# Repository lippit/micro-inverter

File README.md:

# An open-source - community built micro-inverter

## Manifesto 

The project goal are : 

- Having the first open source PV micro-inverter
- Finally a design easy to repair that is no longer a black box
- Redeem your data sovereignty, you will no longer depend on a proprietary cloud to follow your solar production and consumption. 

## Open, for everyone, forever

- This project is propulsed by its community. 
- The collective work generated is meant to remain open. 
- Design files are made with open source software - Namely kiCAD.
- Mechanical interfaces and components are modeled using FreeCAD.
- Simulation files use ngSpice.

In that sense, the owntech foundation aims at protecting this technical common.

## Specifications
This section is inspired from 

Comparison of micro-inverters with rated output power between 350VA and 400VA:

| Model                                  | HM-350 | HM-400 | IQ7A |EVT300  |TSOL-M800  |
|:---------------------------------------|:-----------:|:-----------:|:-----------:|:-------------:|:---------------:|
| Manufacturer                           | Hoymiles    | Hoymiles    | Enphase     | Envertech     |    TSUN         |
| Number of solar panels                 | 1           | 1           | 1           | 1             | 2               |
| Recommended input power (W)            | 280-470+    | 320-540+    | 295-460     | 180-420+      |2 $\cdot$ 280-440|
| $V_{MPPT,min}$ (V)                     | 33          | 34          | 38 (18)     | 24            | 33              |
| $V_{MPPT,max}$ (V)                     | 48          | 48          | 43 (58)     | 45            | 48              |
| Start-up voltage (V)                   | 22          | 22          | 22          | -             | -               |
| Operating volage range (V)             | 16-60       | 16-60       | 16-58       | 18-54         | 16-60           |
| Maximum input current (A)              | 11.5        | 12          | 12          | 12            | 11.5            |
| Maximum input short circuit current (A)| 15          | 15          | 20          | 15            | 15              |
| Rated output power (VA)                | 350         | 400         | 349         | 300           | 600             |
| Peak efficiency (%)                    | 96.7        | 96.7        | 97.7        | 95.4          | 96.7            |
| CEC weighted efficiency (%)            | 96.5        | 96.5        | 97.0        | 95.0          | 96.5            |

### uVerter Target specifications

| Category | Requirement | Notes |
|---|---:|---|
| Grid | 220 V AC to 250V AC / 50 to 60 Hz   | Hardware not compatible with 110V grids |
| Grid compliance | Grid-code compliant | Exact certification scope depends on country / standard |
| Rated apparent power | 450 VA | Software-limited power cap supported |
| Input DC operating range | 16 V – 58 V | PV module operating window |
| Recommended PV input power | 350 W – 550 W | Depends on module and thermal conditions |
| Efficiency | > 95% | Target at nominal conditions |
| Power factor | ≈ 1 | Near-unity PF at rated power |
| THD | < 5% | Total harmonic distortion at rated conditions |
| Isolation | Galvanic isolation | Electrical isolation between PV and grid |
| Operating temperature | -40 °C to +60 °C | Derating may apply |
| Repairability | No invasive potting | Designed to be serviceable / inspectable |
| Connectivity | Wi-Fi | Local-first monitoring (no proprietary cloud required) |

## Renderings

## Control overview

The control overview shows the uVerter as two coordinated stages: a PV-controlled DC/DC front end that regulates the panel operating point and raises the DC bus, followed by an AC control stage that shapes a grid-compliant AC output. Measurements and commands flow through Data I/O and the grid-compliance controller so the inverter can synchronize to line/neutral, limit harmonics, and maintain safe operation while power flows from the PV input to the grid.

## Firmware overview

The `firmware/src/main.cpp` file is the entry point for the uVerter firmware: it configures the sensors and power stages, sets up the real-time and background tasks, and runs the state machine plus control loops that drive the boost and inverter legs based on measurements and synchronization status.

- Real-time control runs in `loop_critical_task()` at 100 µs to read sensors, enforce protections, regulate the boost stage, compute duty cycles, and update grid-sync variables.
- Supervisory logic runs in `loop_application_task()` to manage modes (idle/startup/power/error), handle transitions, and expose telemetry through the user data API.

### Compiling

Micro-inverter uses [PlatformIO](https://platformio.org/) as it's build and dependency management system.

#### From the command line

1. Create and activate a Python virtual environment.

        python3 -m venv .owntech-venv
        source .owntech-venv/bin/activate

2. Install PlatformIO.

        pip3 install platformio

3. Compile the code. Dependencies (including Zephyr and Owntech libraries) are downloaded automatically.

        cd micro-inverter/firmware/
        pio run

#### In Visual Studio Code

1. Install the "PlatformIO IDE" extension
2. Open the `firmware` directory via PlatformIO's home screen (**not** with VSCode's File -> Open)
3. Press the "Build" button in the PlatformIO toolbar (found on the bottom left)

## Contribute 

### Spread the word

- ⭐ Star this repository  

- Share the project with PV / power electronics / open-hardware communities  

- Mention it in meetups, forums, maker spaces, or your local energy co-op  

### Give feedback and report issues

Help us improve by opening GitHub issues:

- Bug reports (schematic/PCB mistakes, BOM mismatches, mechanical interferences)  

- Documentation gaps (unclear steps, missing diagrams, confusing naming)  

- Feature requests  

### Choose a contribution path

Start with  — a living list of work items the community can pick up.  
Whether you’re a student looking for a thesis topic, an engineer wanting to review a safety-critical design, or a maker growing skills in hardware and firmware: you’re welcome here.  

Bring what you have: time, curiosity, test equipment, careful eyes, lived experience installing or repairing PV gear.  
Let’s build an inverter that isn’t a black box — and keep it open, for everyone, forever.  

## Safety first  

### Disclaimer
This project is shared as-is, without any warranty of any kind, and without any guarantee of compliance with safety, EMC, or grid-connection regulations.
By building, modifying, or using this design, you accept full responsibility for verification, testing, certification (if applicable), and safe operation.

Do not connect a prototype to the public grid.
Grid connection must only happen after appropriate validation, protections, and (where required) third-party certification.

### Mind the risks  
Building a micro-inverter is an advanced DIY project. It combines high energy, high voltage, fast switching, and grid interaction — a mix that can injure, start fires, or damage property

Key hazards include:

- Electric shock and electrocution
Internal stages can reach hundreds of volts. Multiple nets are high voltage. Some capacitors can stay charged after power-off. Treat the system as live until proven discharged and measured.

- Fire and thermal runaway
Faults can turn traces, connectors, inductors, or semiconductors into heaters in seconds. Thermal issues can escalate quickly.

### A community note
We want this project to be open — not reckless. If you spot a safety issue (creepage/clearance, insulation, thermal margins, protection logic, connector ratings, etc.), please report it.
Safety improvements are contributions that protect everyone.

## Standards and directives

### Relevant EU directives for CE

- Directive 2001/95/EC: General Product Safety
- Directive 2014/30/EU: Electromagnetic Compatibility (EMC)
- Directive 2014/35/EU: Low Voltage (LVD)
- Directive 2014/53/EU: Radio Equipment (RED)
- Directive 2011/65/EU: Restriction of the use of certain Hazardous Substances (RoHS)

### Low Voltage Directive (LVD)

**EN IEC 62109-1:2010**
Safety of power converters for use in photovoltaic power systems - Part 1: General requirements

**EN IEC 62109-2:2011**
Safety of power converters for use in photovoltaic power systems - Part 2: Particular requirements for inverters

### Electromagnetic Compatibility (EMC)

**EN 62920:2017+A11+A1:2021**
Photovoltaic power generating systems - EMC requirements and test methods for power conversion equipment

**ETSI EN 301 489-1**
ElectroMagnetic Compatibility (EMC) standard for radio equipment and services; Part 1: Common technical requirements

**ETSI EN 301 489-17**
ElectroMagnetic Compatibility (EMC) standard for radio equipment and services; Part 17: Specific conditions for Broadband Data Transmission Systems

### Radio Equipment Directive (RED)

**ETSI EN 300 328 V2.2.2**
Wideband transmission systems; Data transmission equipment operating in the 2,4 GHz band; Harmonised Standard for access to radio spectrum

### Grid Regulations

As grid regulations are country specific, please refer to 

## Licence 

This project is licenced under **CERN-OHL-V2-S** open source hardware licence. Licence file can be found under `License/cern-ohl-v2-s`.

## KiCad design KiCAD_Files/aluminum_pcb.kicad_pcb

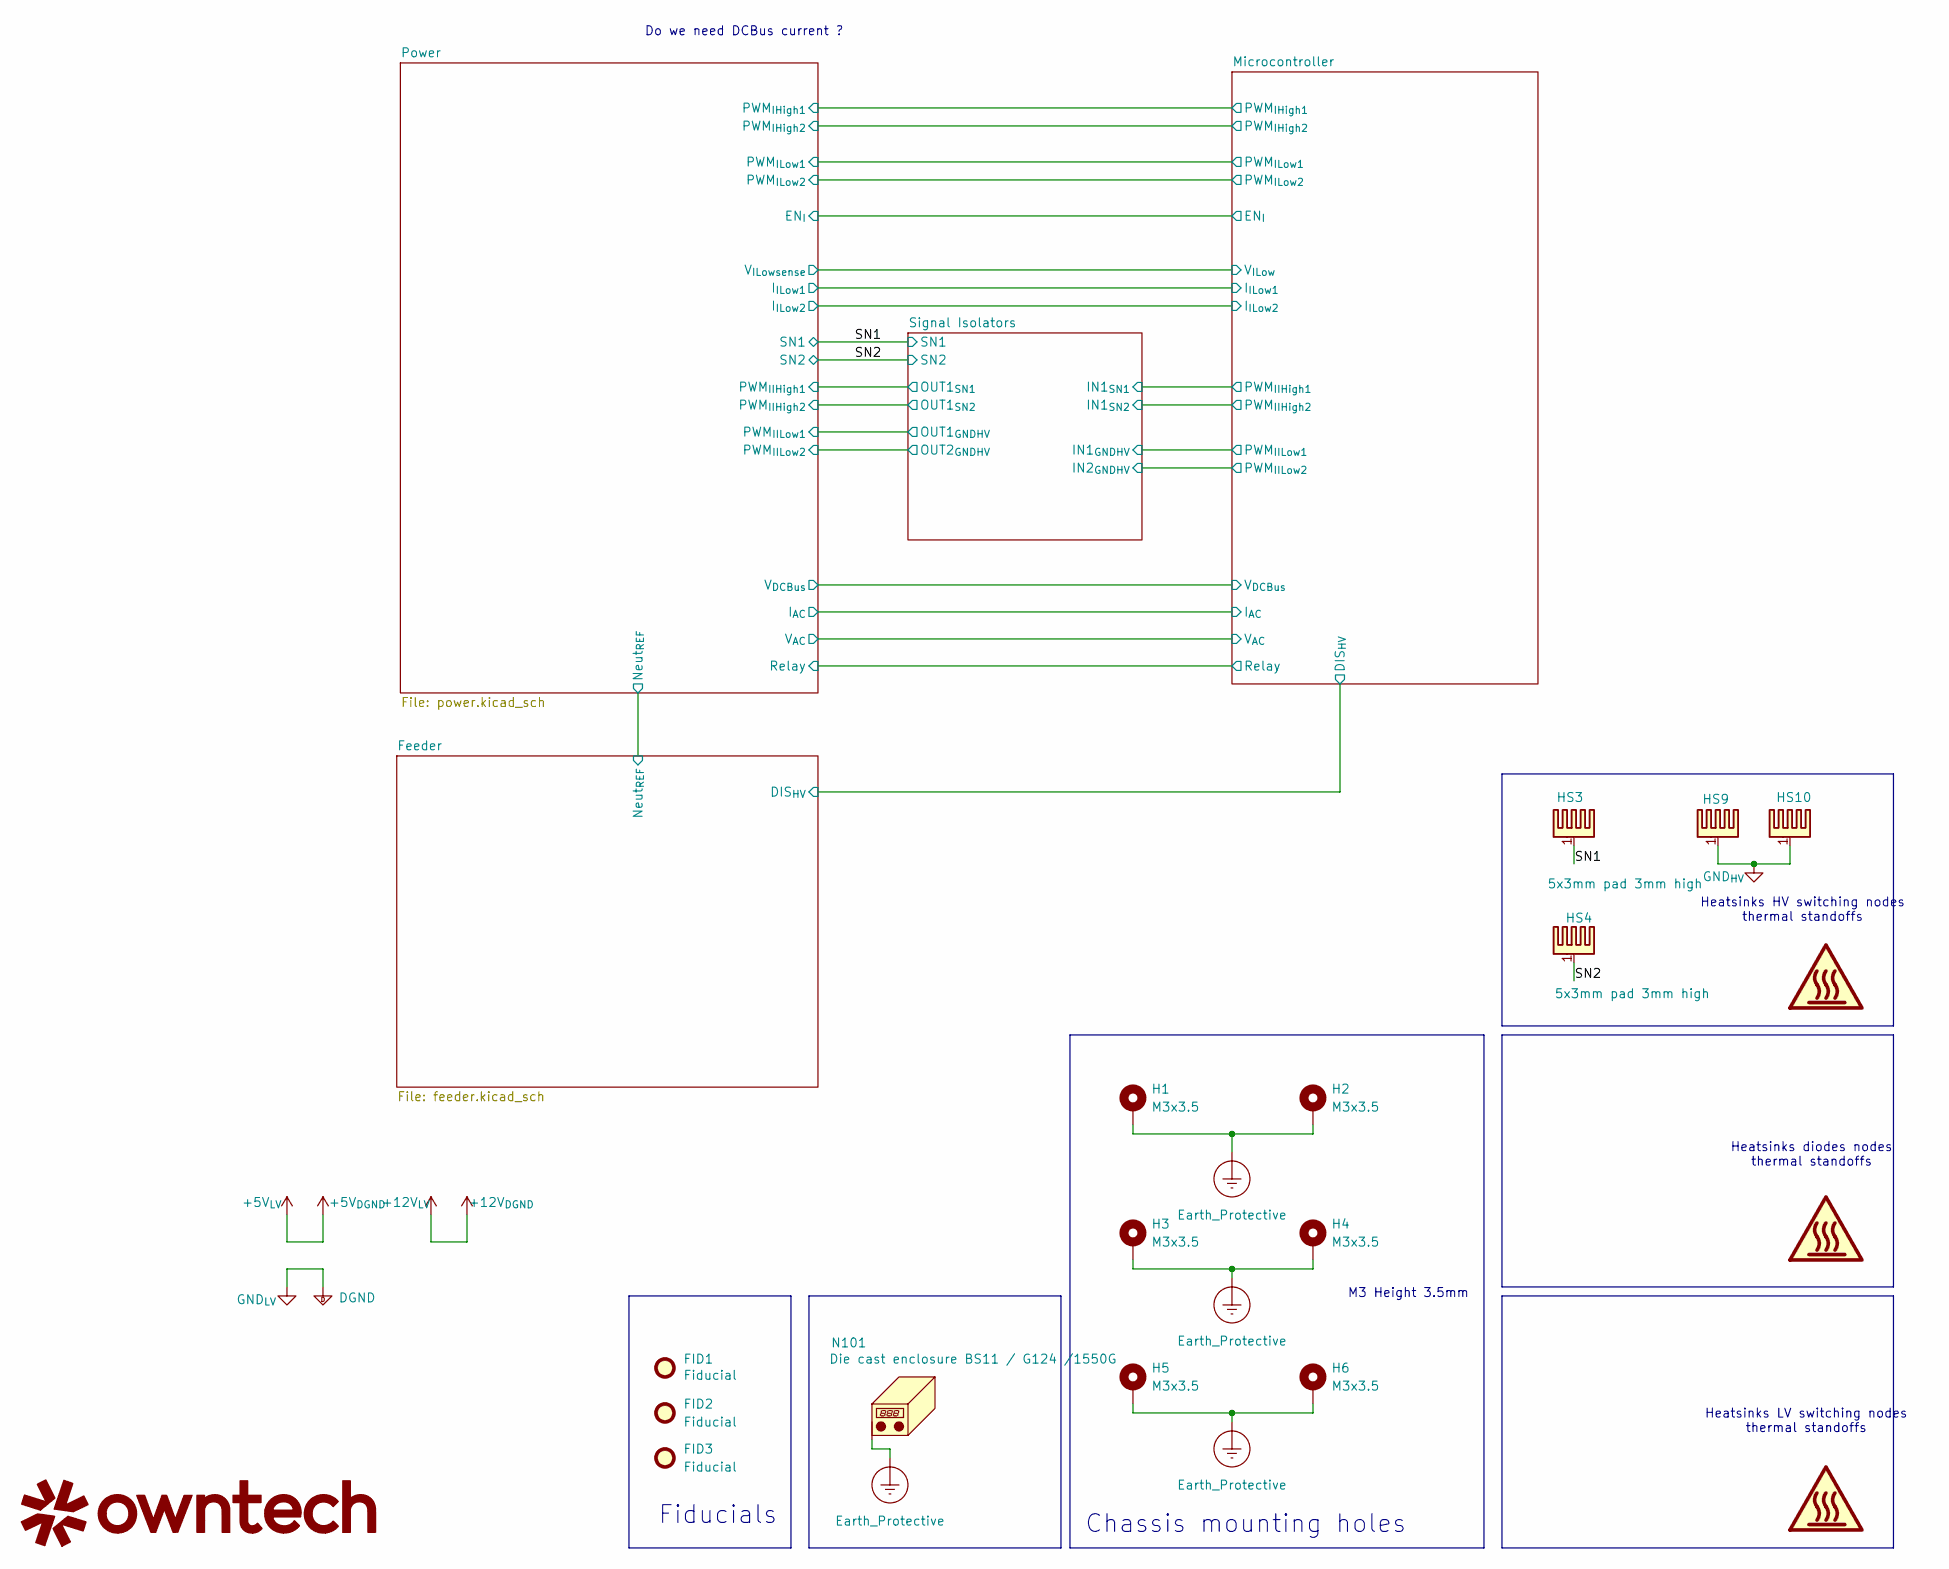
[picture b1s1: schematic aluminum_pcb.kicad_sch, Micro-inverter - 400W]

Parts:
FID1, FID2, FID3: Fiducial; Fiducial_1mm_Mask2mm
H1, H2, H3, H4, H5, H6: M3x3.5; SMD_BD5.6-D4.1; LCSC C2916333
HS3, HS4, HS9, HS10: 5x3mm pad 3mm high; BTC-533-ZN01; LCSC C42404563
Logo1: owntech34mmneg
N101: Die cast enclosure BS11 / G124 /1550G; Die Cast Casing 1550G

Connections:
/SN1: HS3.1; also elsewhere on the board
/SN2: HS4.1; also elsewhere on the board
Earth_Protective: H1.1, H2.1, H3.1, H4.1, H5.1, H6.1, N101.1; also elsewhere on the board
GND_{HV}: HS9.1, HS10.1; also elsewhere on the board

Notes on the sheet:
Heatsinks diodes nodes thermal standoffs
Heatsinks HV switching nodes thermal standoffs
M3 Height 3.5mm
Do we need DCBus current ?
Fiducials
Chassis mounting holes
Heatsinks LV switching nodes thermal standoffs

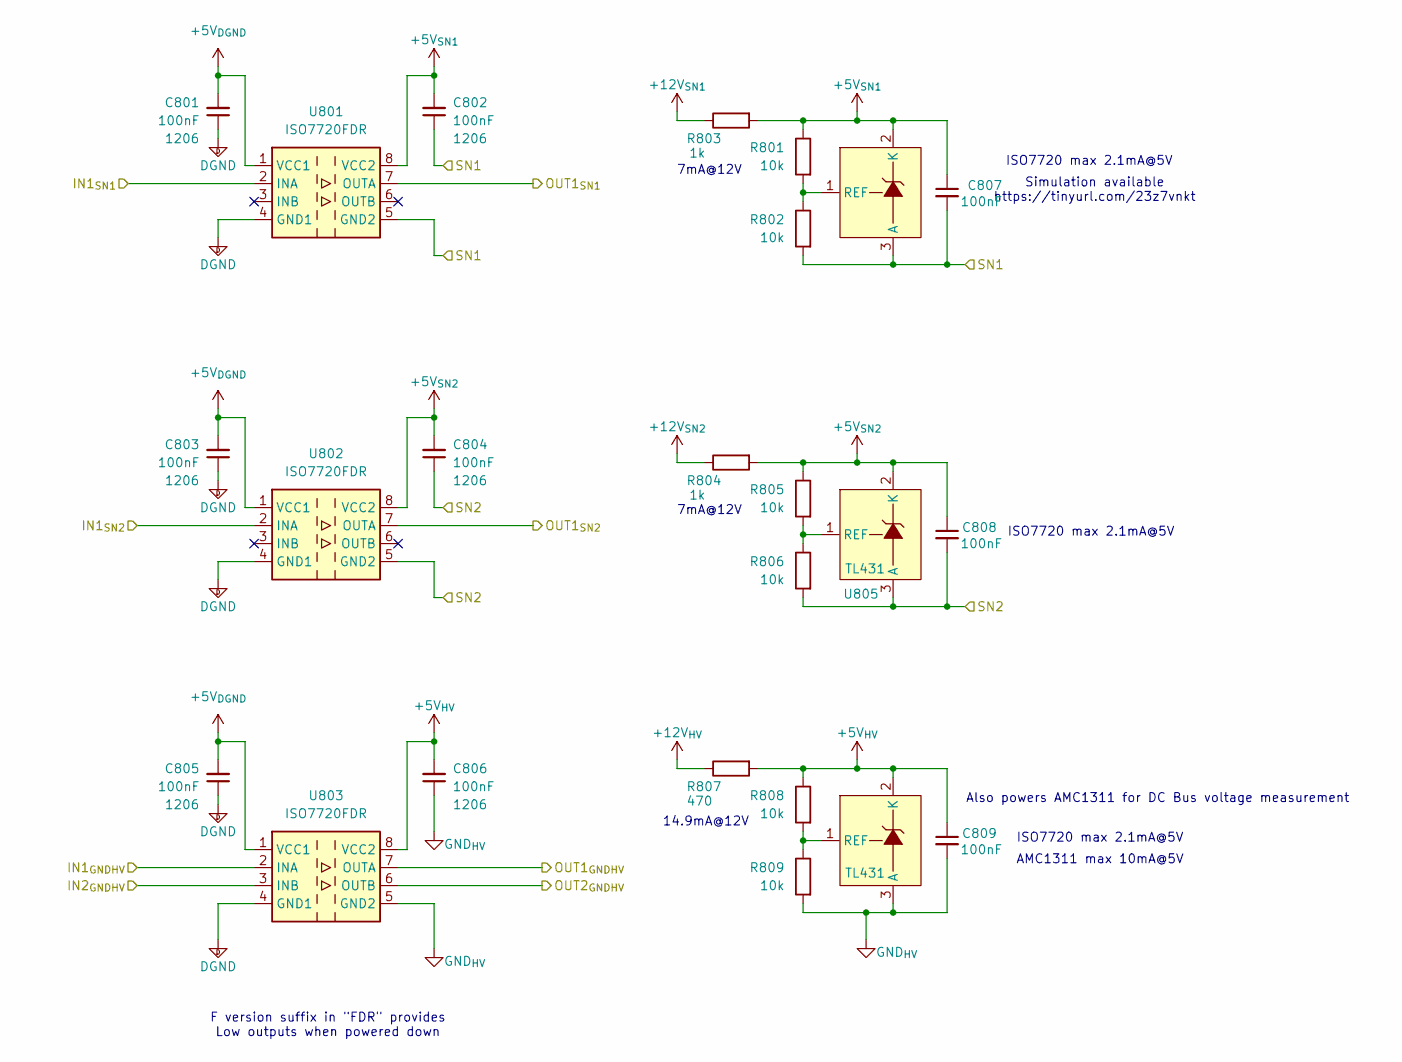
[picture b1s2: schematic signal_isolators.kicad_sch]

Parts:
C801, C802, C803, C805, C806: 100nF; C_1206_3216Metric; Voltage 50V; LCSC C5449000
C804, C807, C808, C809: 100nF; C_0805_2012Metric; Voltage 50V; LCSC C5449000
R801, R802, R805, R806, R808, R809: 10k; C_0805_2012Metric
R803, R804: 1k; C_0805_2012Metric
R807: 470; C_0805_2012Metric
U801, U802, U803: ISO7720FDR; SOIC-8_3.9x4.9mm_P1.27mm; LCSC C2878308
U804: TL431DBZ; SOT-23
U805, U806: TL431; SOT-23

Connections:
+5V_{DGND}: C801.2, C803.2, C805.2, U801.1 (VCC1), U802.1 (VCC1), U803.1 (VCC1); also elsewhere on the board
+5V_{HV}: C806.2, C809.1, R807.2, R808.1, U803.8 (VCC2), U806.2 (K); also elsewhere on the board
+5V_{SN1}: C802.2, C807.1, R801.1, R803.2, U801.8 (VCC2), U804.2 (K)
+5V_{SN2}: C804.2, C808.1, R804.2, R805.1, U802.8 (VCC2), U805.2 (K)
+12V_{HV}: R807.1; also elsewhere on the board
+12V_{SN1}: R803.1; also elsewhere on the board
+12V_{SN2}: R804.1; also elsewhere on the board
/Microcontroller/PWM_{IIHigh1}: U801.2 (INA); also elsewhere on the board
/Microcontroller/PWM_{IIHigh2}: U802.2 (INA); also elsewhere on the board
/Microcontroller/PWM_{IILow1}: U803.2 (INA); also elsewhere on the board
/Microcontroller/PWM_{IILow2}: U803.3 (INB); also elsewhere on the board
/Power/PWM_{IIHigh1}: U801.7 (OUTA); also elsewhere on the board
/Power/PWM_{IIHigh2}: U802.7 (OUTA); also elsewhere on the board
/Power/PWM_{IILow1}: U803.7 (OUTA); also elsewhere on the board
/Power/PWM_{IILow2}: U803.6 (OUTB); also elsewhere on the board
/SN1: C802.1, C807.2, R802.2, U801.5 (GND2), U804.3 (A); also elsewhere on the board
/SN2: C804.1, C808.2, R806.2, U802.5 (GND2), U805.3 (A); also elsewhere on the board
GND_{HV}: C806.1, C809.2, R809.2, U803.5 (GND2), U806.3 (A); also elsewhere on the board
unnamed: R801.2, R802.1, U804.1 (REF)
unnamed: R805.2, R806.1, U805.1 (REF)
unnamed: R808.2, R809.1, U806.1 (REF)

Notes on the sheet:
ISO7720 max 2.1mA@5V
Also powers AMC1311 for DC Bus voltage measurement
Simulation available https://tinyurl.com/23z7vnkt
AMC1311 max 10mA@5V
7mA@12V
14.9mA@12V
F version suffix in "FDR" provides Low outputs when powered down

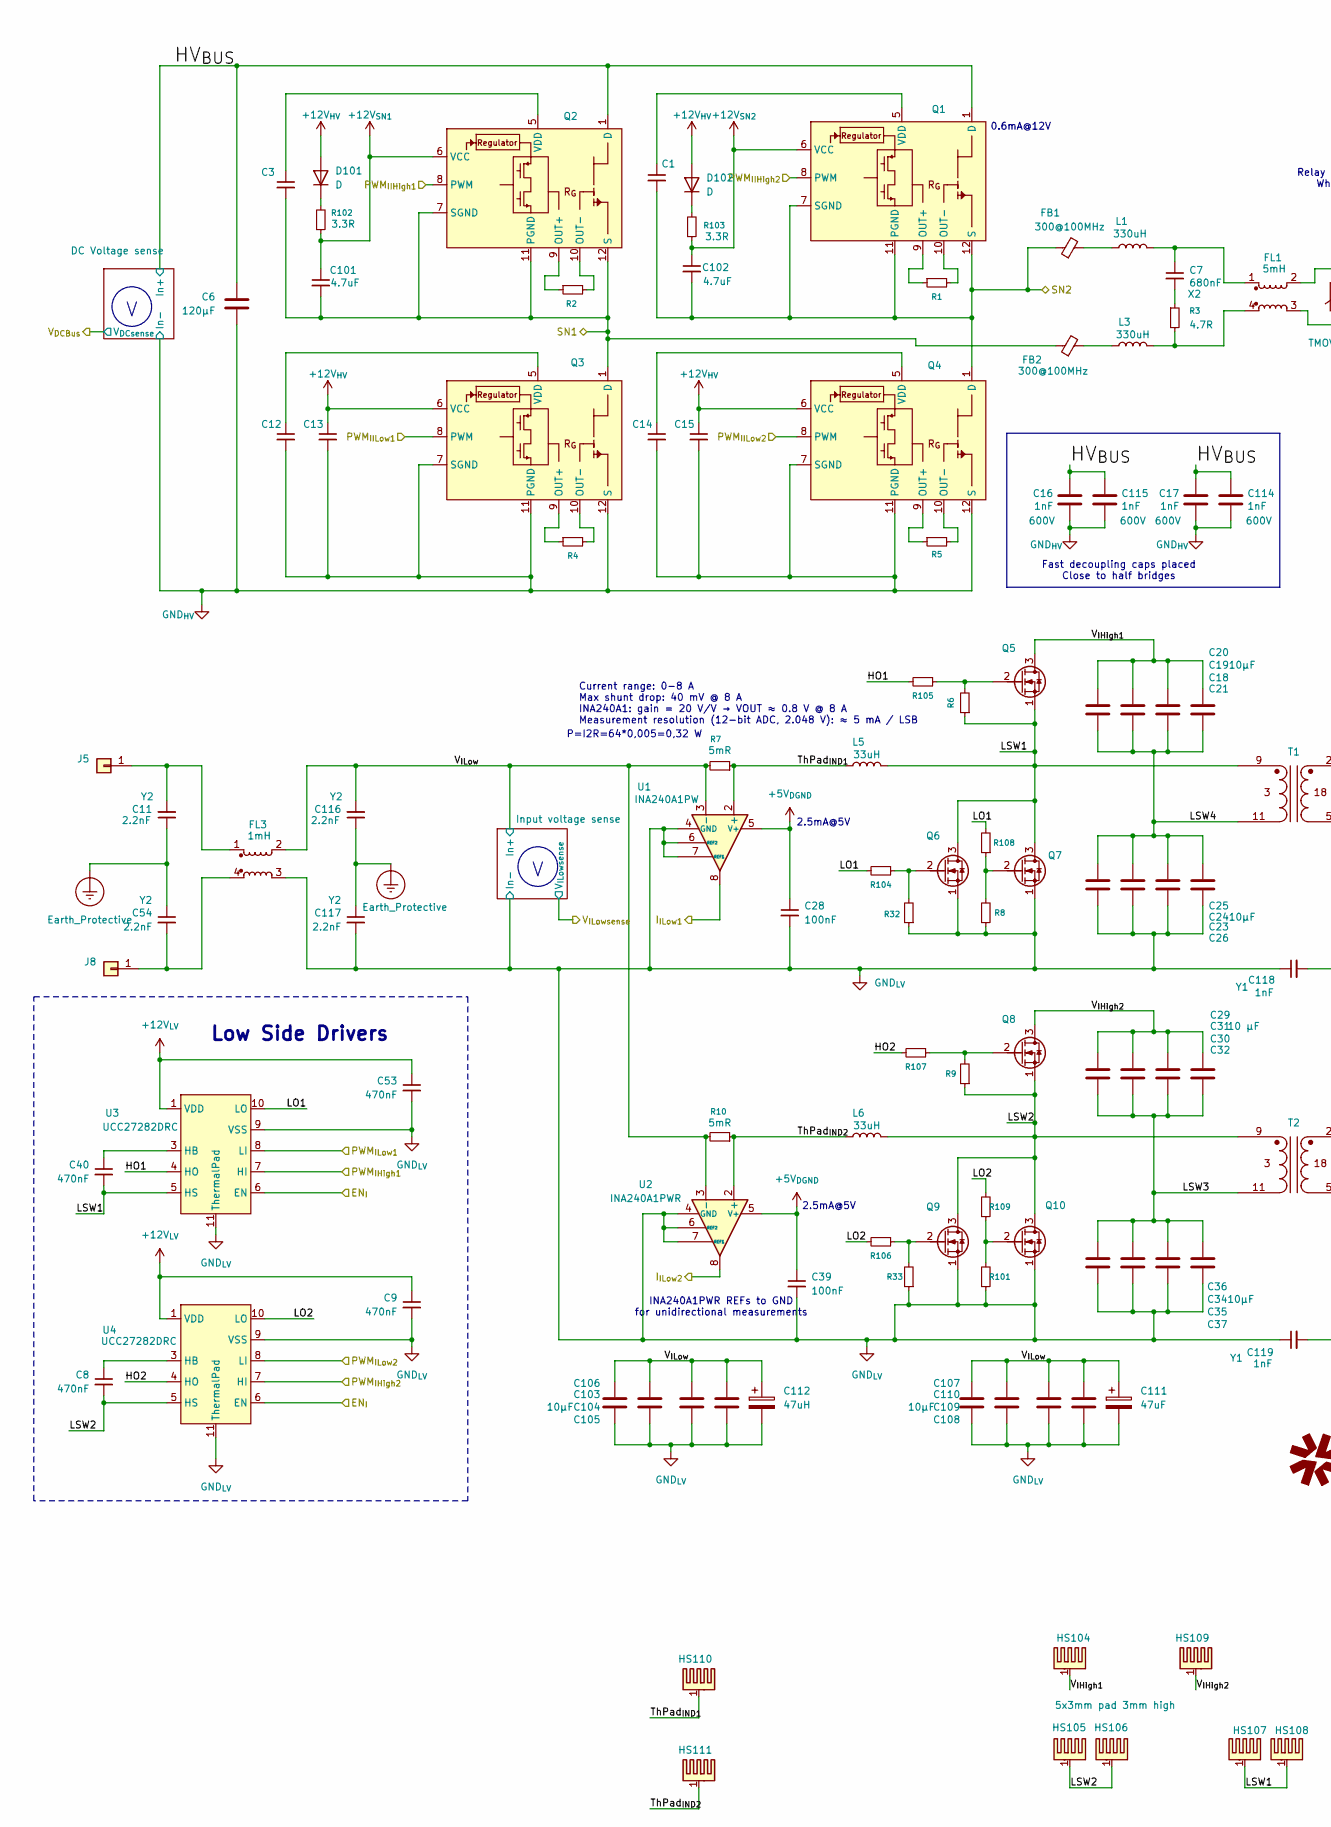
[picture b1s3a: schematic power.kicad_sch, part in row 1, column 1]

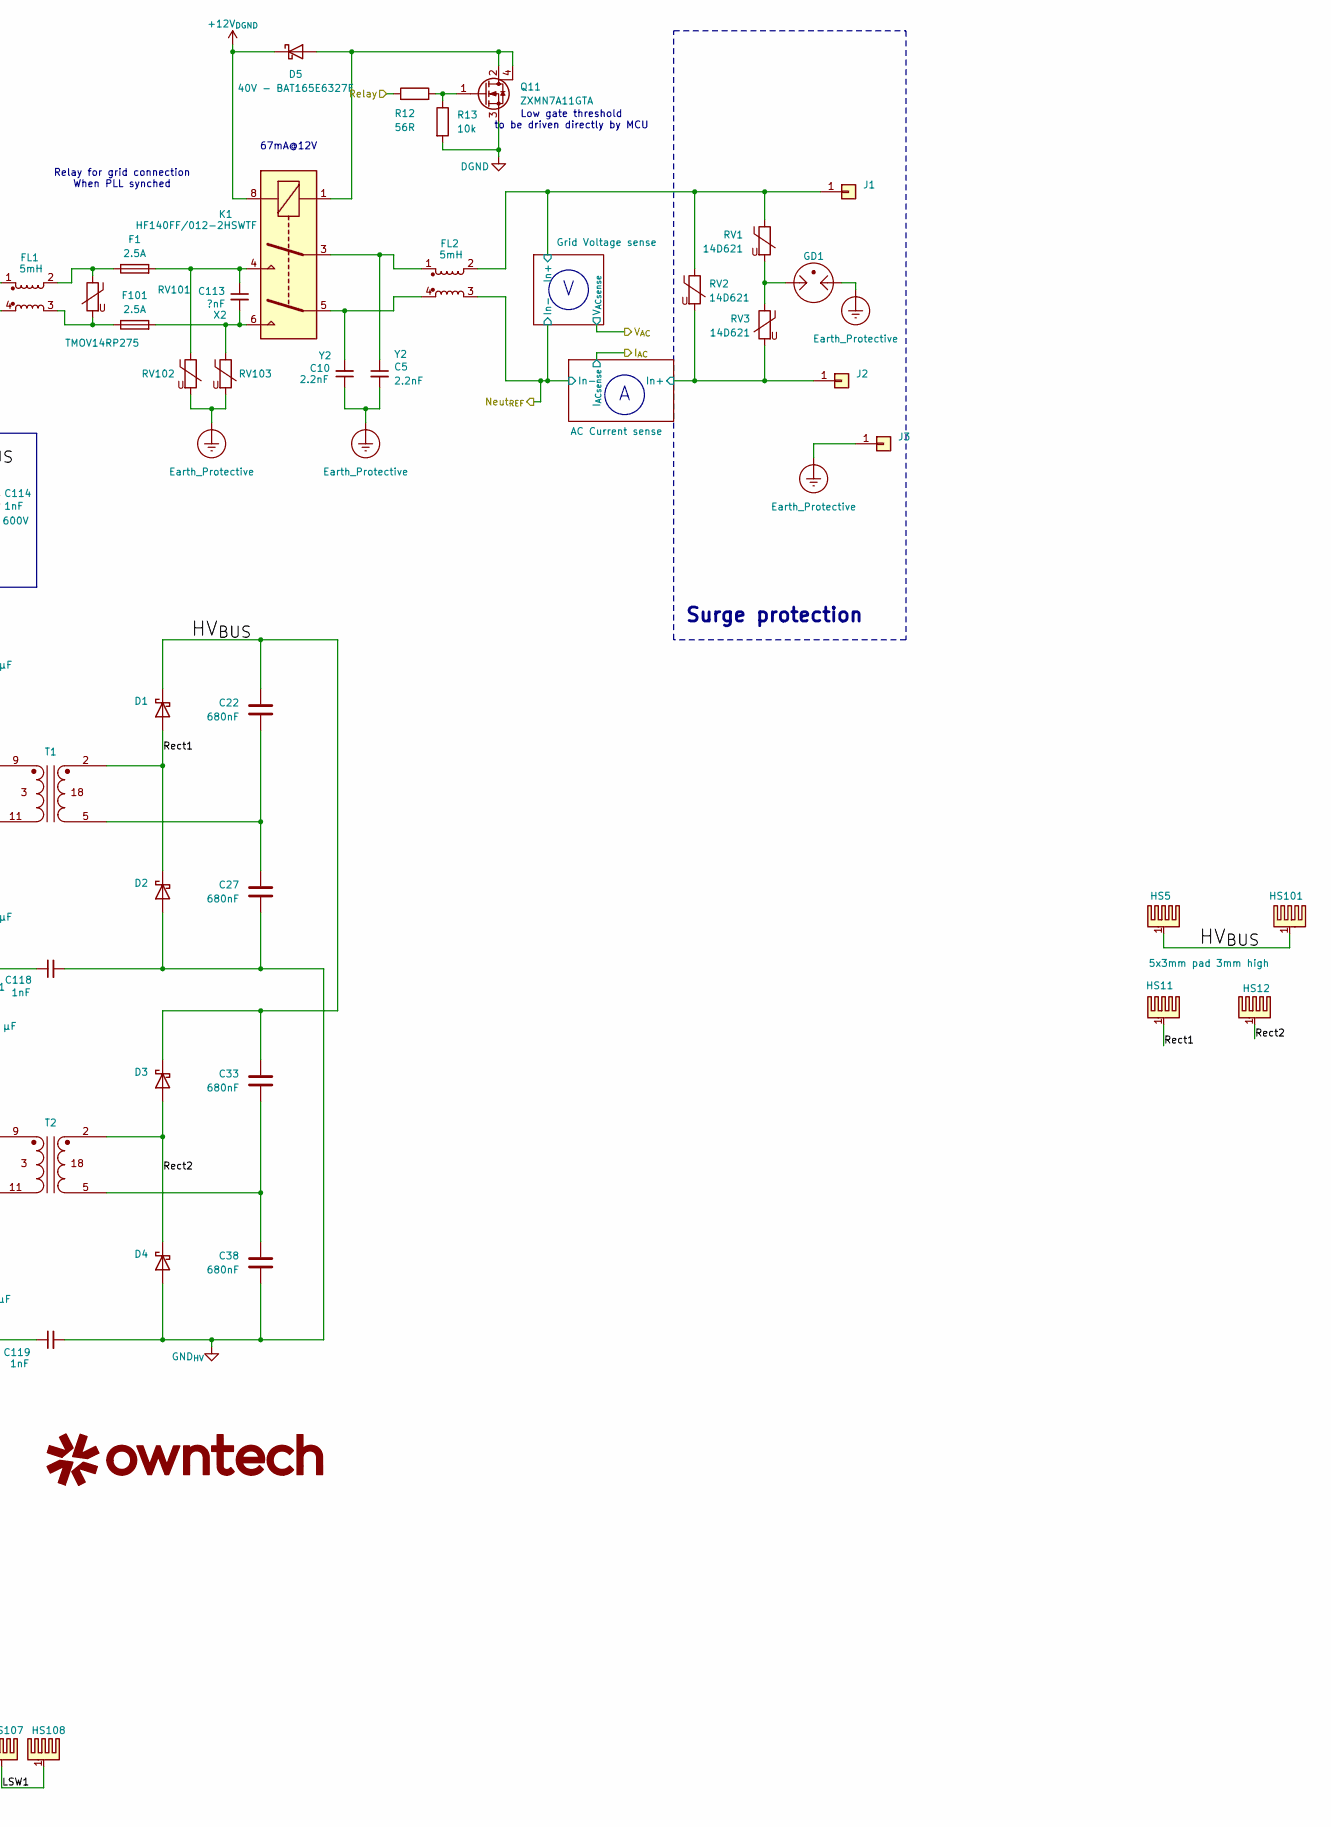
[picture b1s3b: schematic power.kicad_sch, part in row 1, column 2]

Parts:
C1, C3, C12, C13, C14, C15: C_Small; C_0805_2012Metric
C5, C10, C11, C54, C116, C117: 2.2nF; C_Rect_L9.0mm_W4.0mm_P7.50mm_MKT; LCSC C5121878
C6: 120µF; film_capacitors; LCSC C783662
C7: 680nF; C_Rect_L16.5mm_W8.7mm_P15.00mm_MKT; LCSC C489081
C8, C9, C40, C53: 470nF; C_0603_1608Metric
C16, C17, C114, C115: 1nF; C_1210_3225Metric; Voltage 200V
C18, C25, C34, C103, C110: 10µF; C_1206_3216Metric; LCSC C5449000
C19, C20, C21, C23, C24, C26, C29, C30, C32, C35, C36, C37, C104, C105, C106, C107, C108, C109: C; C_1206_3216Metric; LCSC C5449000
C22, C27, C33, C38: 680nF; C_Rect_L16.5mm_W8mm_P15.00mm_MKT; LCSC C7529558
C28, C39: 100nF; C_0805_2012Metric
C31: 10 µF; C_1206_3216Metric; LCSC C5449000
C101, C102: 4.7uF; C_0805_2012Metric
C111: 47uF; C_Elec_10x10.2; LCSC C3031594
C112: 47uH; C_Elec_10x10.2; LCSC C3031594
C113: ?nF; C_Rect_L16.5mm_W7.0mm_P15.00mm_MKT; LCSC C489081
C118, C119: 1nF; CAP-TH_L6.3-W4.4-P10.00-D0.6-S3.8; LCSC C2974845
D1, D2, D3, D4: D_Schottky; Diode_TO-252-2; LCSC C967703
D5: 40V - BAT165E6327F; D_SOD-323; LCSC C42411276
D101, D102: D; D_SOD-123
F1, F101: 2.5A; FUSE-TH_L8.4-W4.1-P5.08-D0.6; LCSC C2995772
FB1, FB2: 300@100MHz; L_1206_3216Metric; LCSC C703115
FL1, FL2: 5mH; FILTER-TH_XRSQ1515-5MH-V-1013; LCSC C30584795
FL3: 1mH; IND-TH_4P-L23.0-W15.0-P7.50-D1.0-S9.0; LCSC C30584795
GD1: 2R600B-8S; SMD_GDT; LCSC C42246321
HS5, HS11, HS12, HS101, HS104, HS105, HS106, HS107, HS108, HS109, HS110, HS111: 5x3mm pad 3mm high; BTC-533-ZN01; LCSC C42404563
J1, J2, J3, J5, J8: Conn_01x01; SMD-4_TS34056055-0440; LCSC C19724594
K1: HF140FF/012-2HSWTF; RELAY-TH_HF140FF-024-2HSWT; LCSC C5322766
L1, L3: 330uH; IND-SMD_L27.0-W19.5-LS23.5_60B104C; LCSC C42422423
L5, L6: 33uH; SRP1510CA-330M; LCSC C18236320
Logo101: owntech_mini10
Q1, Q2, Q3, Q4: CID12N65D; DFN-10_L8.0-W6.0_CID12N65D; LCSC C21547657
Q5, Q6, Q7, Q8, Q9, Q10: CJAC90SN12; DFN-8-1EP_5x6_P1.27mm; LCSC C504097
Q11: ZXMN7A11GTA; SOT-223; LCSC C460277
R1, R2, R4, R5: R_Small; R_0805_2012Metric
R3: 4.7R; R_2512_6332Metric; LCSC C2897629
R6, R9: 10k; R_0603_1608Metric
R7, R10: 5mR; R_2512_6332Metric; LCSC C393074
R8, R32, R33, R101, R109: 20k; R_0603_1608Metric
R12: 56R; C_0805_2012Metric
R13: 10k; C_0805_2012Metric
R102, R103: 3.3R; R_0805_2012Metric
R104, R105, R106, R107, R108: 20; R_0603_1608Metric
RV1, RV2, RV3: 14D621; RV_Disc_D15.5mm_W11mm_P7.5mm; LCSC C774640
RV101, RV102, RV103: TMOV14RP275; RV_Disc_D12mm_W6.2mm_P7.5mm; LCSC C1528070
T1, T2: Transformer_1P_1S; RM12
U1: INA240A1PW; TSSOP-8_4.4x3mm_P0.65mm; LCSC C93965
U2: INA240A1PWR; TSSOP-8_4.4x3mm_P0.65mm; LCSC C93965
U3, U4: UCC27282DRC; VSON-10_L3.0-W3.0-P0.50-TL-EP; LCSC C2677035

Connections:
+5V_{DGND}: C28.1, C39.1, U1.5 (V+), U2.5 (V+); also elsewhere on the board
+12V_{HV}: C13.1, C15.1, D101.2 (A), D102.2 (A), Q3.6 (VCC), Q4.6 (VCC); also elsewhere on the board
+12V_{SN1}: C101.1, Q2.6 (VCC), R102.1; also elsewhere on the board
+12V_{SN2}: C102.1, Q1.6 (VCC), R103.1; also elsewhere on the board
/Feeder/Neut_{REF}: FL2.3; also elsewhere on the board
/Microcontroller/EN_{I}: U3.6 (EN), U4.6 (EN); also elsewhere on the board
/Microcontroller/I_{ILow1}: U1.8; also elsewhere on the board
/Microcontroller/I_{ILow2}: U2.8; also elsewhere on the board
/Microcontroller/PWM_{IHigh1}: U3.7 (HI); also elsewhere on the board
/Microcontroller/PWM_{IHigh2}: U4.7 (HI); also elsewhere on the board
/Microcontroller/PWM_{ILow1}: U3.8 (LI); also elsewhere on the board
/Microcontroller/PWM_{ILow2}: U4.8 (LI); also elsewhere on the board
/Microcontroller/Relay: R12.1; also elsewhere on the board
/Power/AC Current sense/In+: J2.1, RV2.2, RV3.2; also elsewhere on the board
/Power/Grid Voltage sense/In+: FL2.2, J1.1, RV1.1, RV2.1; also elsewhere on the board
/Power/HO1: R105.2, U3.4 (HO)
/Power/HO2: R107.2, U4.4 (HO)
/Power/HV_{BUS}: C6.1, C16.1, C17.1, C22.1, C33.1, C114.1, C115.1, D1.1 (K), D3.1 (K), HS5.1, HS101.1, Q1.1 (D), Q1.4, Q2.1 (D), Q2.4; also elsewhere on the board
/Power/LO1: R104.2, R108.2, U3.10 (LO)
/Power/LO2: R106.2, R109.2, U4.10 (LO)
/Power/LSW1: C40.2, HS107.1, HS108.1, L5.2, Q5.1 (S), Q6.3 (D), Q7.3 (D), R6.1, T1.8 (AA), T1.9 (AA), U3.5 (HS)
/Power/LSW2: C8.2, HS105.1, HS106.1, L6.2, Q8.1 (S), Q9.3 (D), Q10.3 (D), R9.1, T2.8 (AA), T2.9 (AA), U4.5 (HS)
/Power/LSW3: C29.2, C30.2, C31.2, C32.2, C34.1, C35.1, C36.1, C37.1, T2.11 (AB), T2.12 (AB)
/Power/LSW4: C18.2, C19.2, C20.2, C21.2, C23.1, C24.1, C25.1, C26.1, T1.11 (AB), T1.12 (AB)
/Power/PWM_{IIHigh1}: Q2.8 (PWM); also elsewhere on the board
/Power/PWM_{IIHigh2}: Q1.8 (PWM); also elsewhere on the board
/Power/PWM_{IILow1}: Q3.8 (PWM); also elsewhere on the board
/Power/PWM_{IILow2}: Q4.8 (PWM); also elsewhere on the board
/Power/Rect1: D1.2 (A), D2.1 (K), HS11.1, T1.2 (SB)
/Power/Rect2: D3.2 (A), D4.1 (K), HS12.1, T2.2 (SB)
/Power/ThPad_{IND1}: HS110.1, L5.1, R7.1, U1.2 (+)
/Power/ThPad_{IND2}: HS111.1, L6.1, R10.1, U2.2 (+)
/Power/V_{IHigh1}: C18.1, C19.1, C20.1, C21.1, HS104.1, Q5.3 (D)
/Power/V_{IHigh2}: C29.1, C30.1, C31.1, C32.1, HS109.1, Q8.3 (D)
/Power/V_{ILow}: C103.2, C104.2, C105.2, C106.2, C107.2, C108.2, C109.2, C110.2, C111.1, C112.1, C116.2, FL3.2, R7.2, R10.2, U1.3 (-), U2.3 (-); also elsewhere on the board
/SN1: C3.2, C101.2, FB2.1, Q2.7 (SGND), Q2.11 (PGND), Q2.12 (S), Q3.1 (D), Q3.4; also elsewhere on the board
/SN2: C1.2, C102.2, FB1.1, Q1.7 (SGND), Q1.11 (PGND), Q1.12 (S), Q4.1 (D), Q4.4; also elsewhere on the board
Earth_Protective: C5.2, C10.1, C11.1, C54.1, C116.1, C117.1, GD1.1, J3.1, RV102.2, RV103.2; also elsewhere on the board
GND_{HV}: C6.2, C12.2, C13.2, C14.2, C15.2, C16.2, C17.2, C27.2, C38.2, C114.2, C115.2, C118.2, C119.2, D2.2 (A), D4.2 (A), Q3.7 (SGND), Q3.11 (PGND), Q3.12 (S), Q4.7 (SGND), Q4.11 (PGND), Q4.12 (S); also elsewhere on the board
unnamed: C5.1, FL2.1, K1.3
unnamed: C7.1, FL1.1, L1.2
unnamed: C7.2, R3.1
unnamed: C10.2, FL2.4, K1.5
unnamed: C113.1, F1.2, K1.4, RV102.1
unnamed: C113.2, F101.2, K1.6, RV103.1
unnamed: D5.2 (A), K1.1, Q11.2 (D), Q11.4 (D)
unnamed: D101.1 (K), R102.2
unnamed: D102.1 (K), R103.2
unnamed: F1.1, FL1.2, RV101.1
unnamed: F101.1, FL1.3, RV101.2
unnamed: FB1.2, L1.1
unnamed: FB2.2, L3.1
unnamed: FL1.4, L3.2, R3.2
unnamed: GD1.3, RV1.2, RV3.1
unnamed: C11.2, FL3.1, J5.1
unnamed: C54.2, FL3.4, J8.1
unnamed: Q1.9 (OUT+), R1.1
unnamed: Q1.10 (OUT-), R1.2
unnamed: C1.1, Q1.5 (VDD)
unnamed: Q2.9 (OUT+), R2.1
unnamed: Q2.10 (OUT-), R2.2
unnamed: C3.1, Q2.5 (VDD)
unnamed: Q3.9 (OUT+), R4.1
unnamed: Q3.10 (OUT-), R4.2
unnamed: C12.1, Q3.5 (VDD)
unnamed: Q4.9 (OUT+), R5.1
unnamed: Q4.10 (OUT-), R5.2
unnamed: C14.1, Q4.5 (VDD)
unnamed: Q5.2 (G), R6.2, R105.1
unnamed: Q6.2 (G), R32.2, R104.1
unnamed: Q7.2 (G), R8.2, R108.1
unnamed: Q8.2 (G), R9.2, R107.1
unnamed: Q9.2 (G), R33.2, R106.1
unnamed: Q10.2 (G), R101.2, R109.1
unnamed: Q11.1 (G), R12.2, R13.1
unnamed: C22.2, C27.1, T1.5 (SA)
unnamed: C33.2, C38.1, T2.5 (SA)
unnamed: C40.1, U3.3 (HB)
unnamed: C8.1, U4.3 (HB)

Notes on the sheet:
Surge protection
P=I2R=64*0,005=0,32 W
Low gate threshold to be driven directly by MCU
2.5mA@5V
Current range: 0-8 A Max shunt drop: 40 mV @ 8 A INA240A1: gain = 20 V/V → VOUT ≈ 0.8 V @ 8 A Measurement resolution (12-bit ADC, 2.048 V): ≈ 5 mA / LSB
Low Side Drivers
67mA@12V
Fast decoupling caps placed Close to half bridges
INA240A1PWR REFs to GND for unidirectional measurements
Relay for grid connection When PLL synched
0.6mA@12V

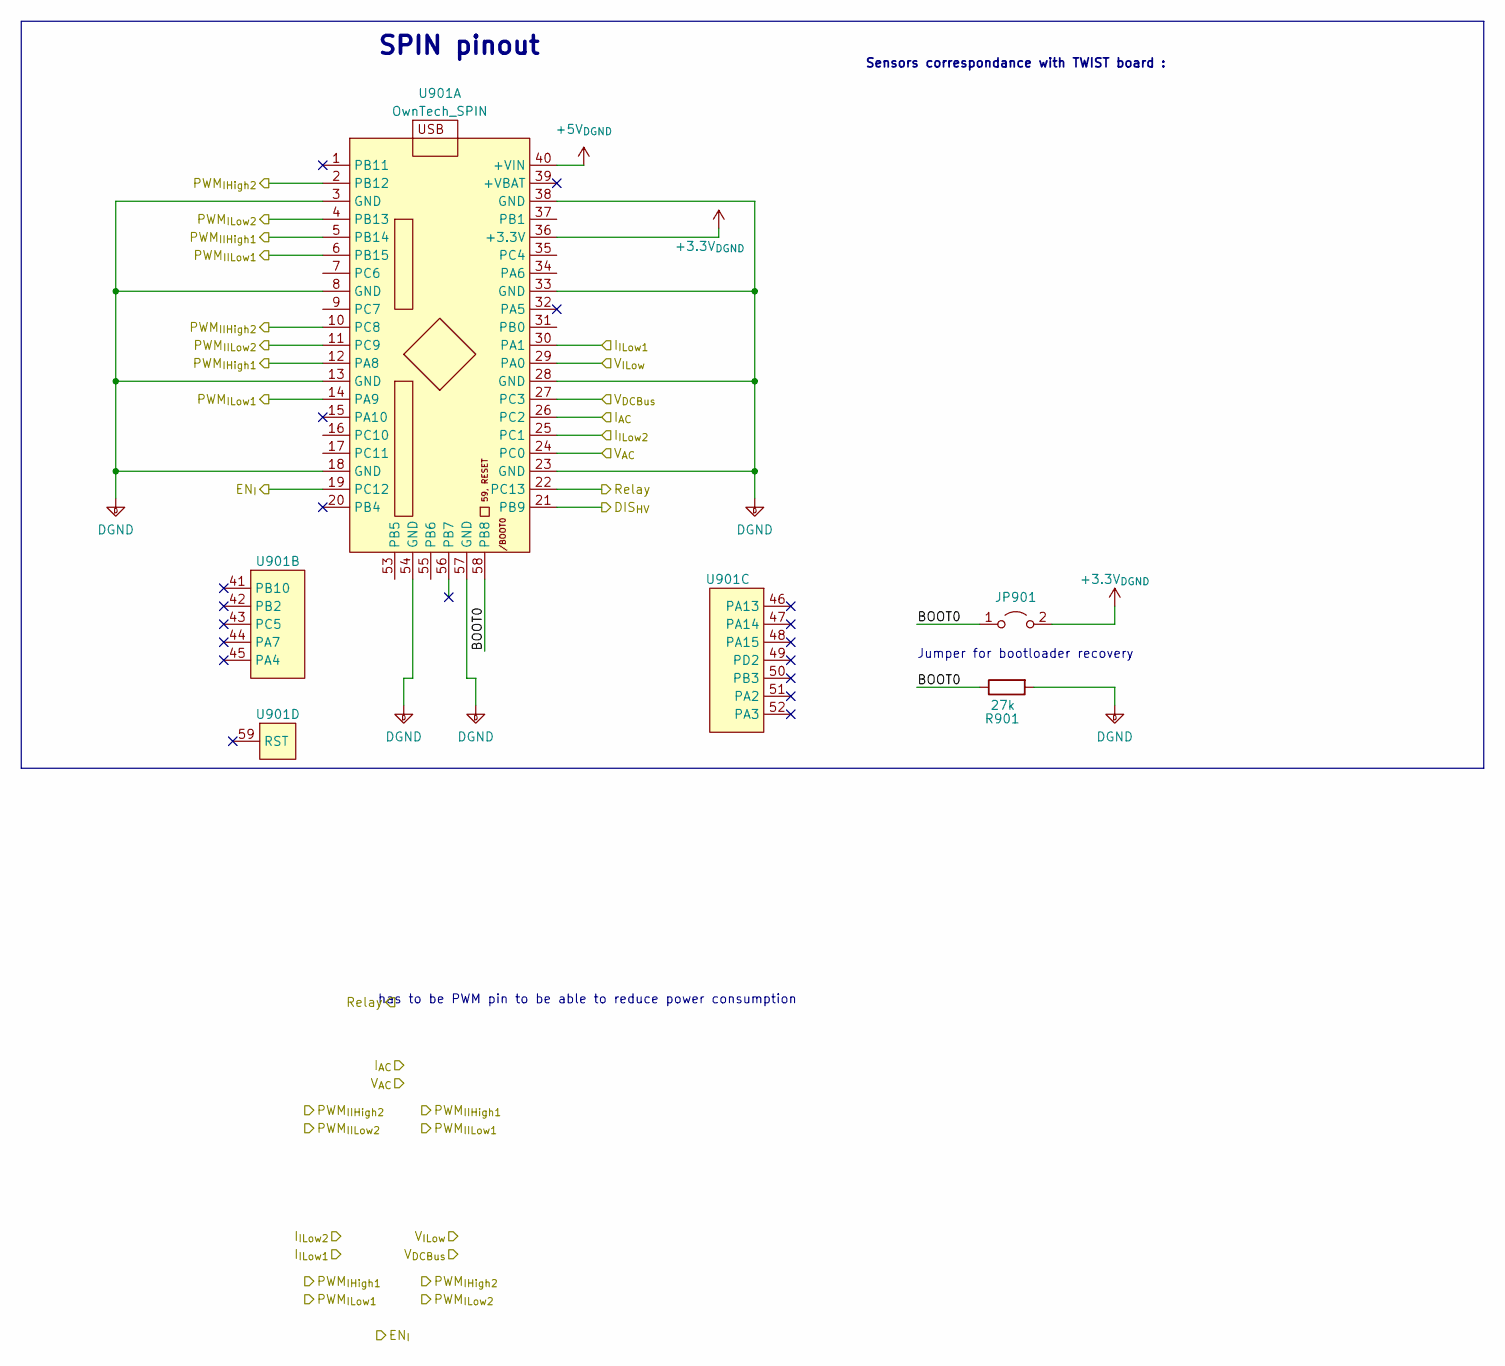
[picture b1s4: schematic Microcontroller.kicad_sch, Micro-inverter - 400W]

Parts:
JP901: Jumper_2_Open; PinHeader_1x02_P2.54mm_Vertical
R901: 27k; R_0805_2012Metric
U901: OwnTech_SPIN; OwnTech_SPINTHT_1

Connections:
+3.3V_{DGND}: JP901.2 (B), U901.36 (+3.3V)
+5V_{DGND}: U901.40 (+VIN); also elsewhere on the board
/Feeder/DIS_{HV}: U901.21 (PB9); also elsewhere on the board
/Microcontroller/BOOT0: JP901.1 (A), R901.1, U901.58 (PB8)
/Microcontroller/EN_{I}: U901.19 (PC12); also elsewhere on the board
/Microcontroller/I_{AC}: U901.26 (PC2); also elsewhere on the board
/Microcontroller/I_{ILow1}: U901.30 (PA1); also elsewhere on the board
/Microcontroller/I_{ILow2}: U901.25 (PC1); also elsewhere on the board
/Microcontroller/PWM_{IHigh1}: U901.12 (PA8); also elsewhere on the board
/Microcontroller/PWM_{IHigh2}: U901.2 (PB12); also elsewhere on the board
/Microcontroller/PWM_{IIHigh1}: U901.5 (PB14); also elsewhere on the board
/Microcontroller/PWM_{IIHigh2}: U901.10 (PC8); also elsewhere on the board
/Microcontroller/PWM_{IILow1}: U901.6 (PB15); also elsewhere on the board
/Microcontroller/PWM_{IILow2}: U901.11 (PC9); also elsewhere on the board
/Microcontroller/PWM_{ILow1}: U901.14 (PA9); also elsewhere on the board
/Microcontroller/PWM_{ILow2}: U901.4 (PB13); also elsewhere on the board
/Microcontroller/Relay: U901.22 (PC13); also elsewhere on the board
/Microcontroller/V_{AC}: U901.24 (PC0); also elsewhere on the board
/Microcontroller/V_{DCBus}: U901.27 (PC3); also elsewhere on the board
/Microcontroller/V_{ILow}: U901.29 (PA0); also elsewhere on the board

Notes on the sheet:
Jumper for bootloader recovery
has to be PWM pin to be able to reduce power consumption
Sensors correspondance with TWIST board :
SPIN pinout
